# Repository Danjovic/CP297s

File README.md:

# CP297s
ZX97 lite board for CP200s case

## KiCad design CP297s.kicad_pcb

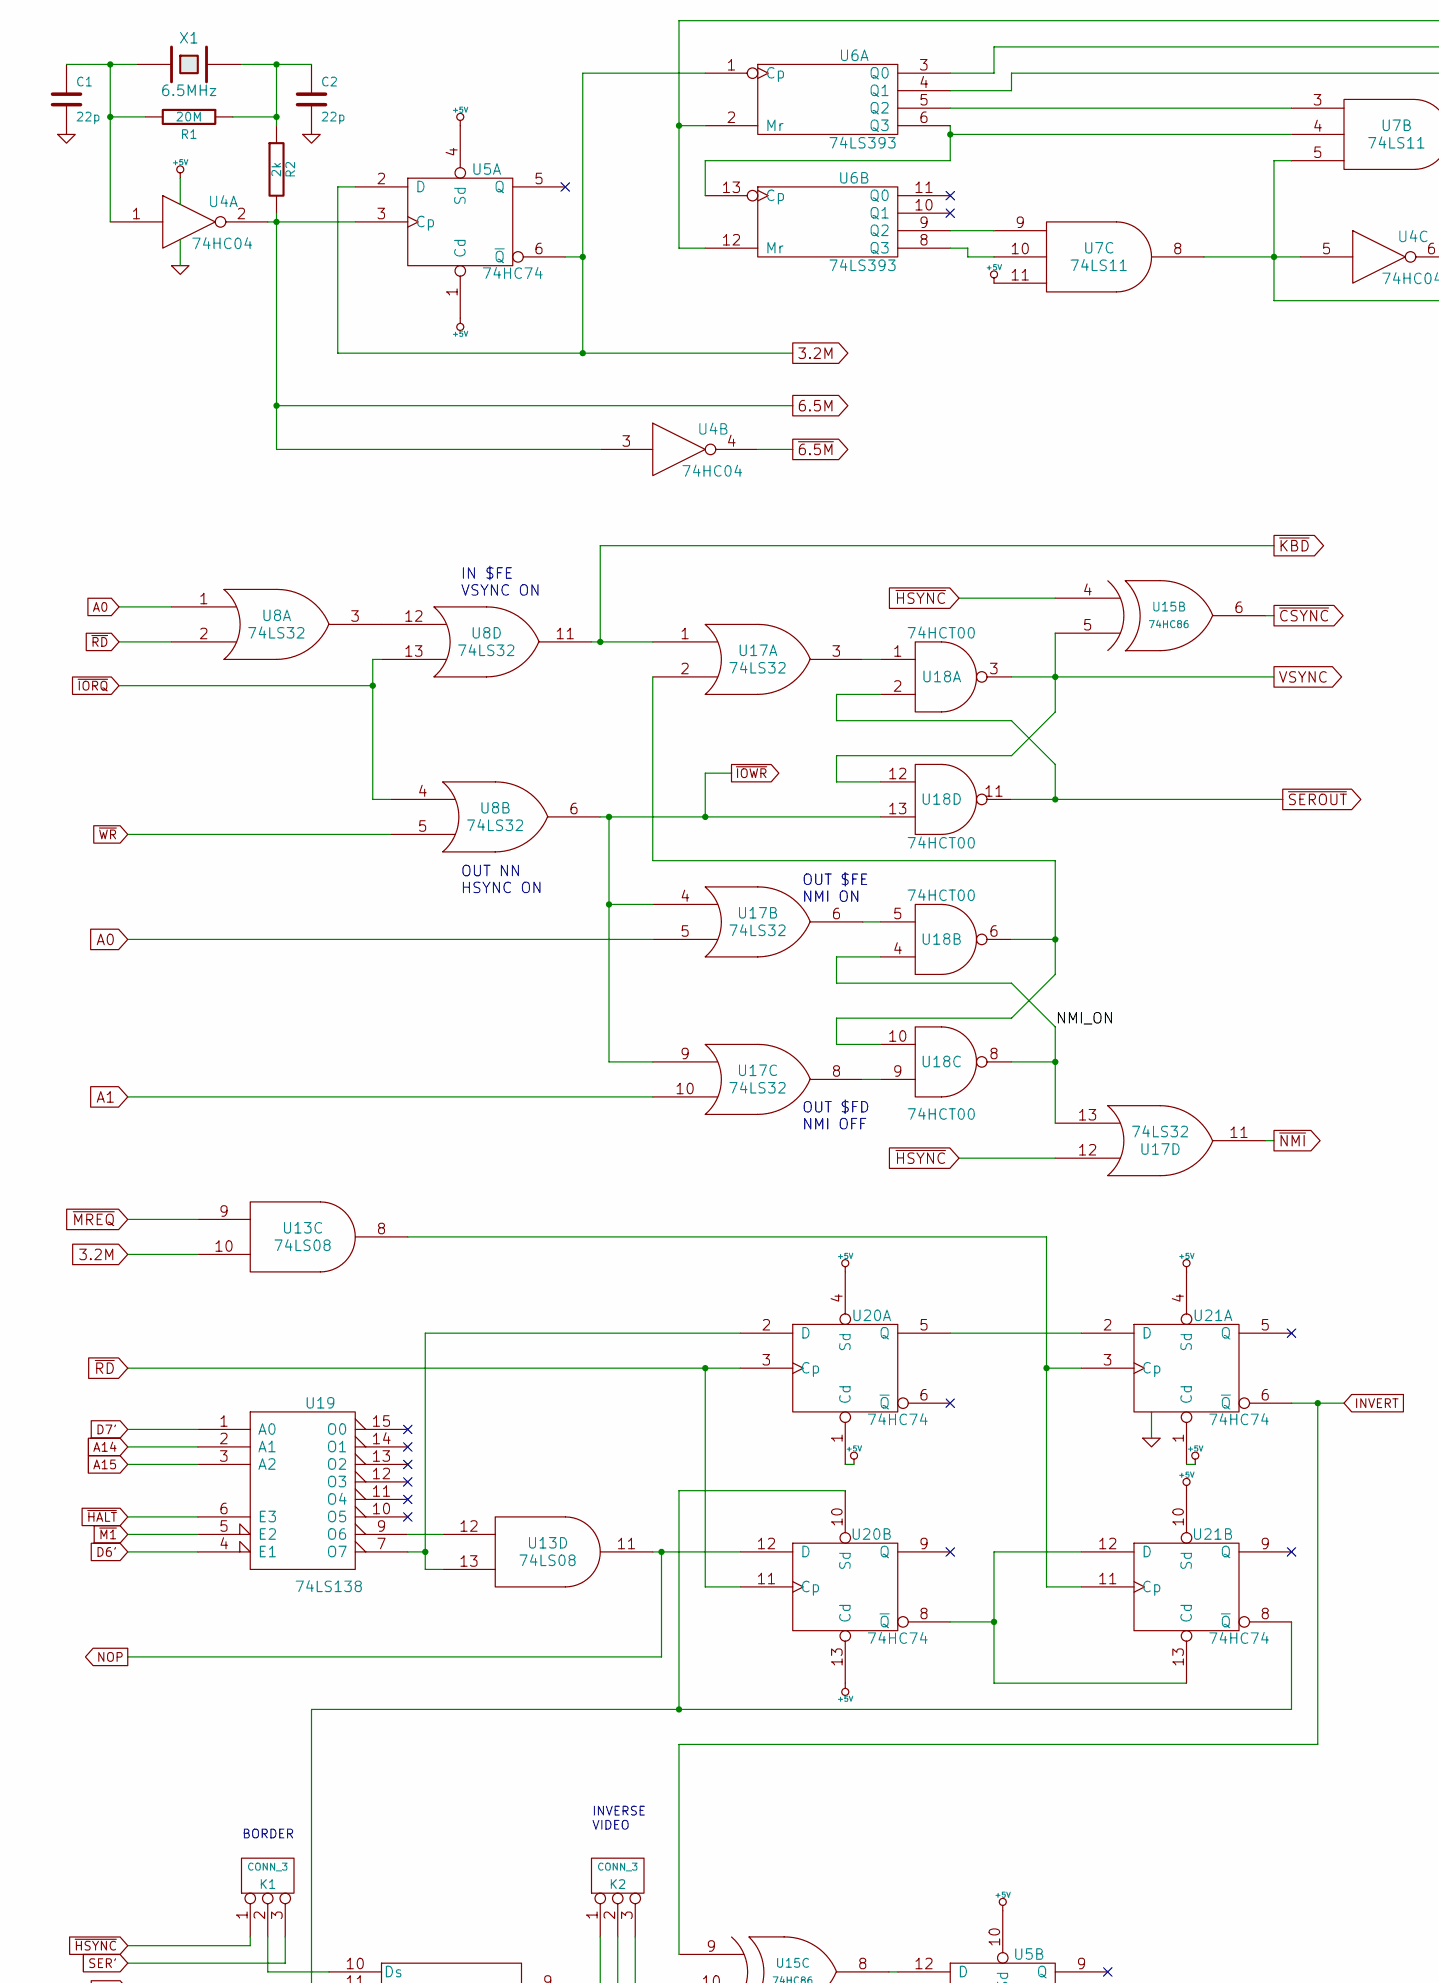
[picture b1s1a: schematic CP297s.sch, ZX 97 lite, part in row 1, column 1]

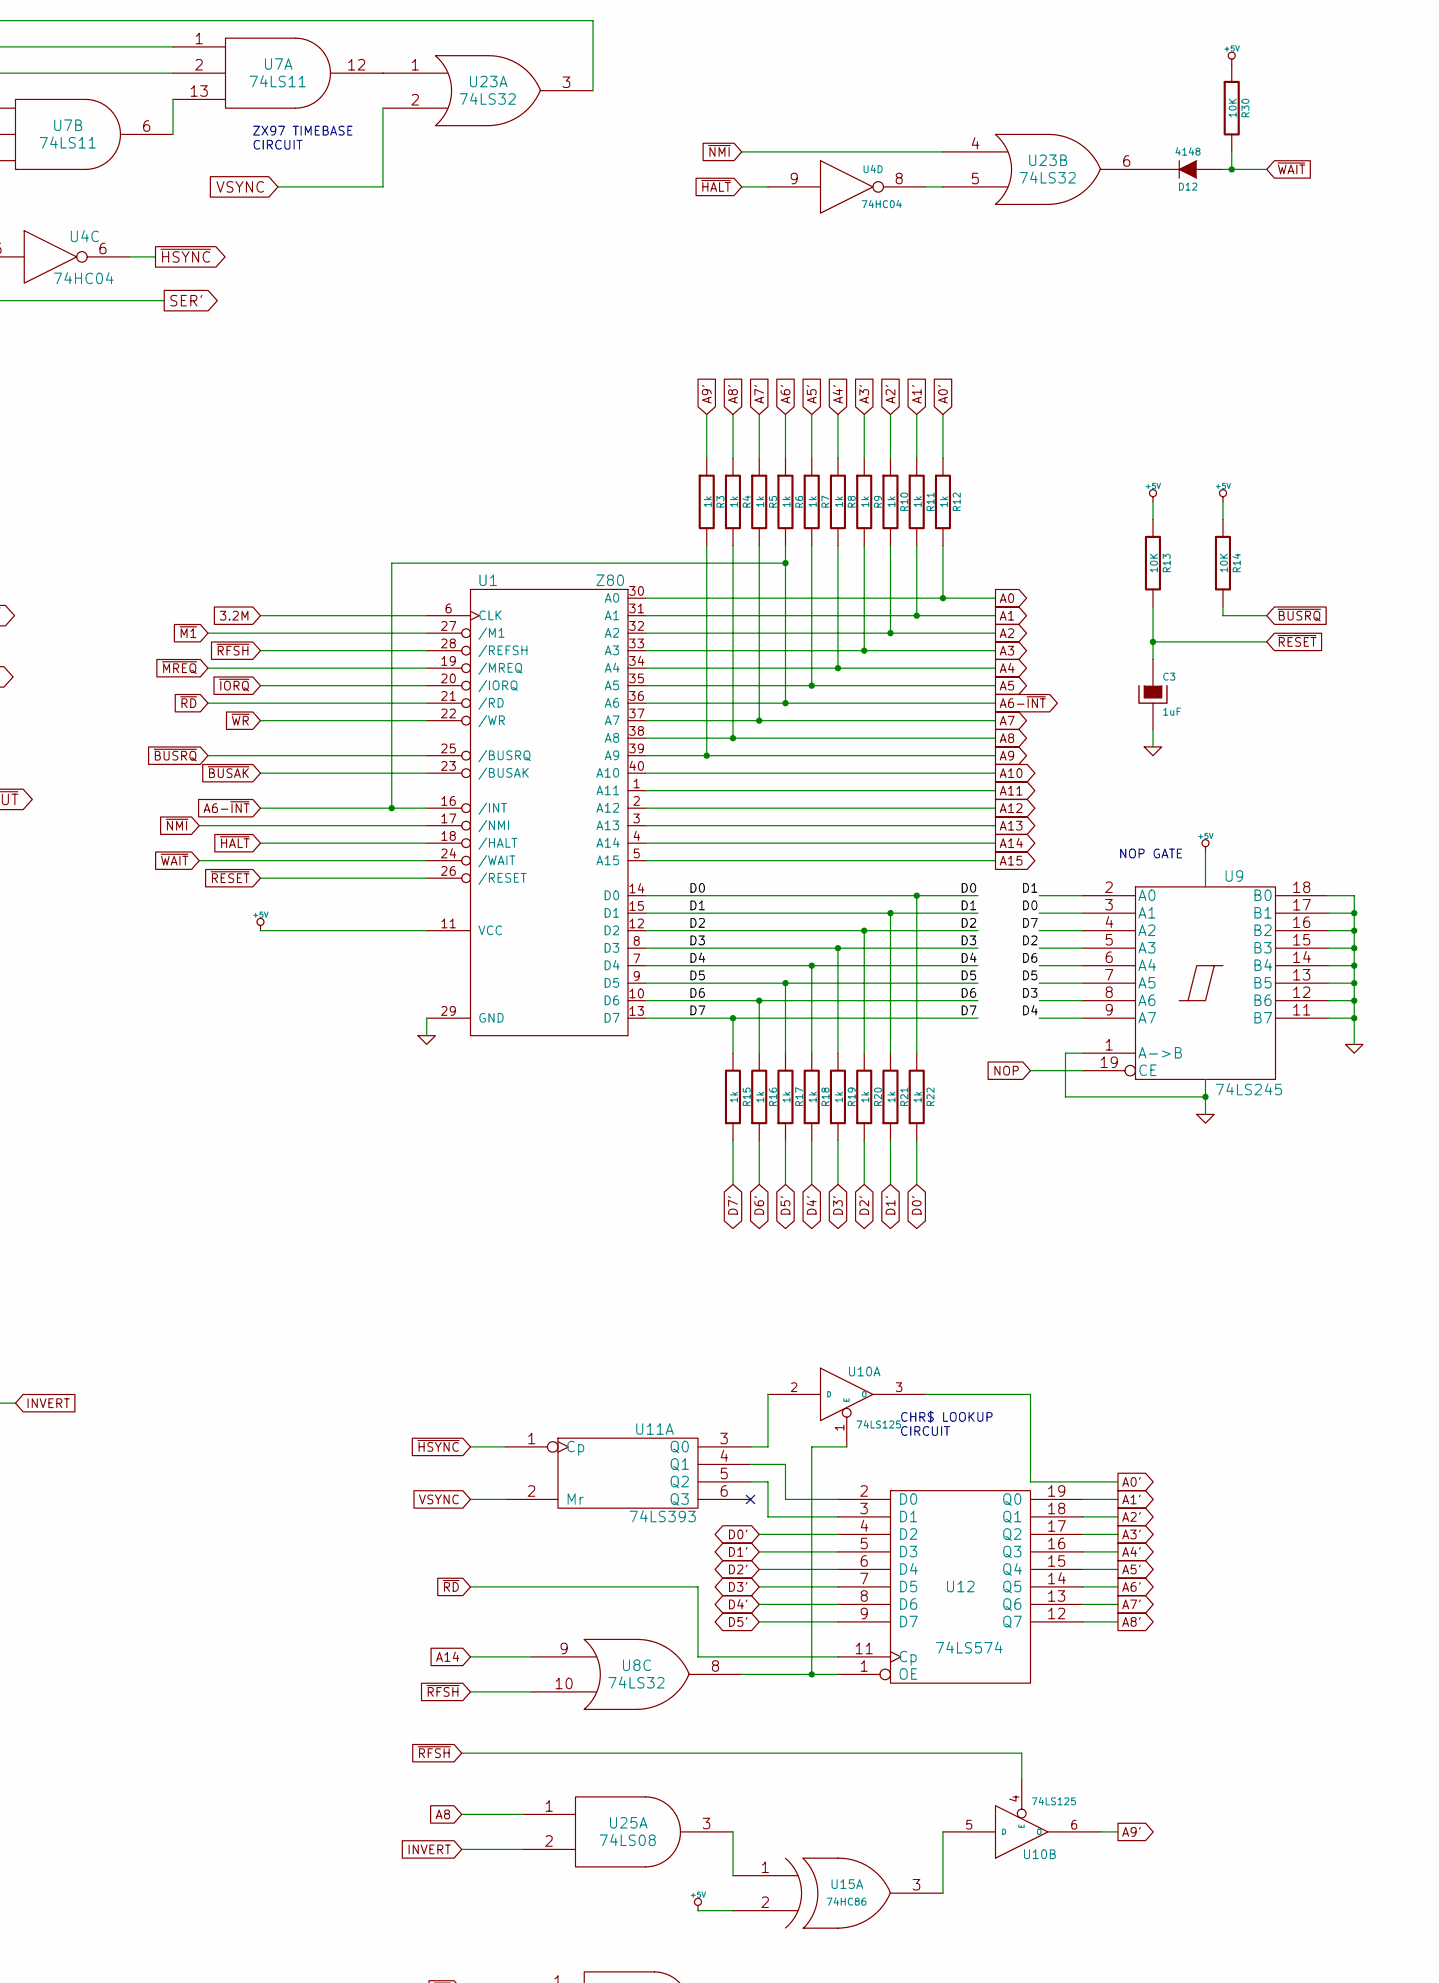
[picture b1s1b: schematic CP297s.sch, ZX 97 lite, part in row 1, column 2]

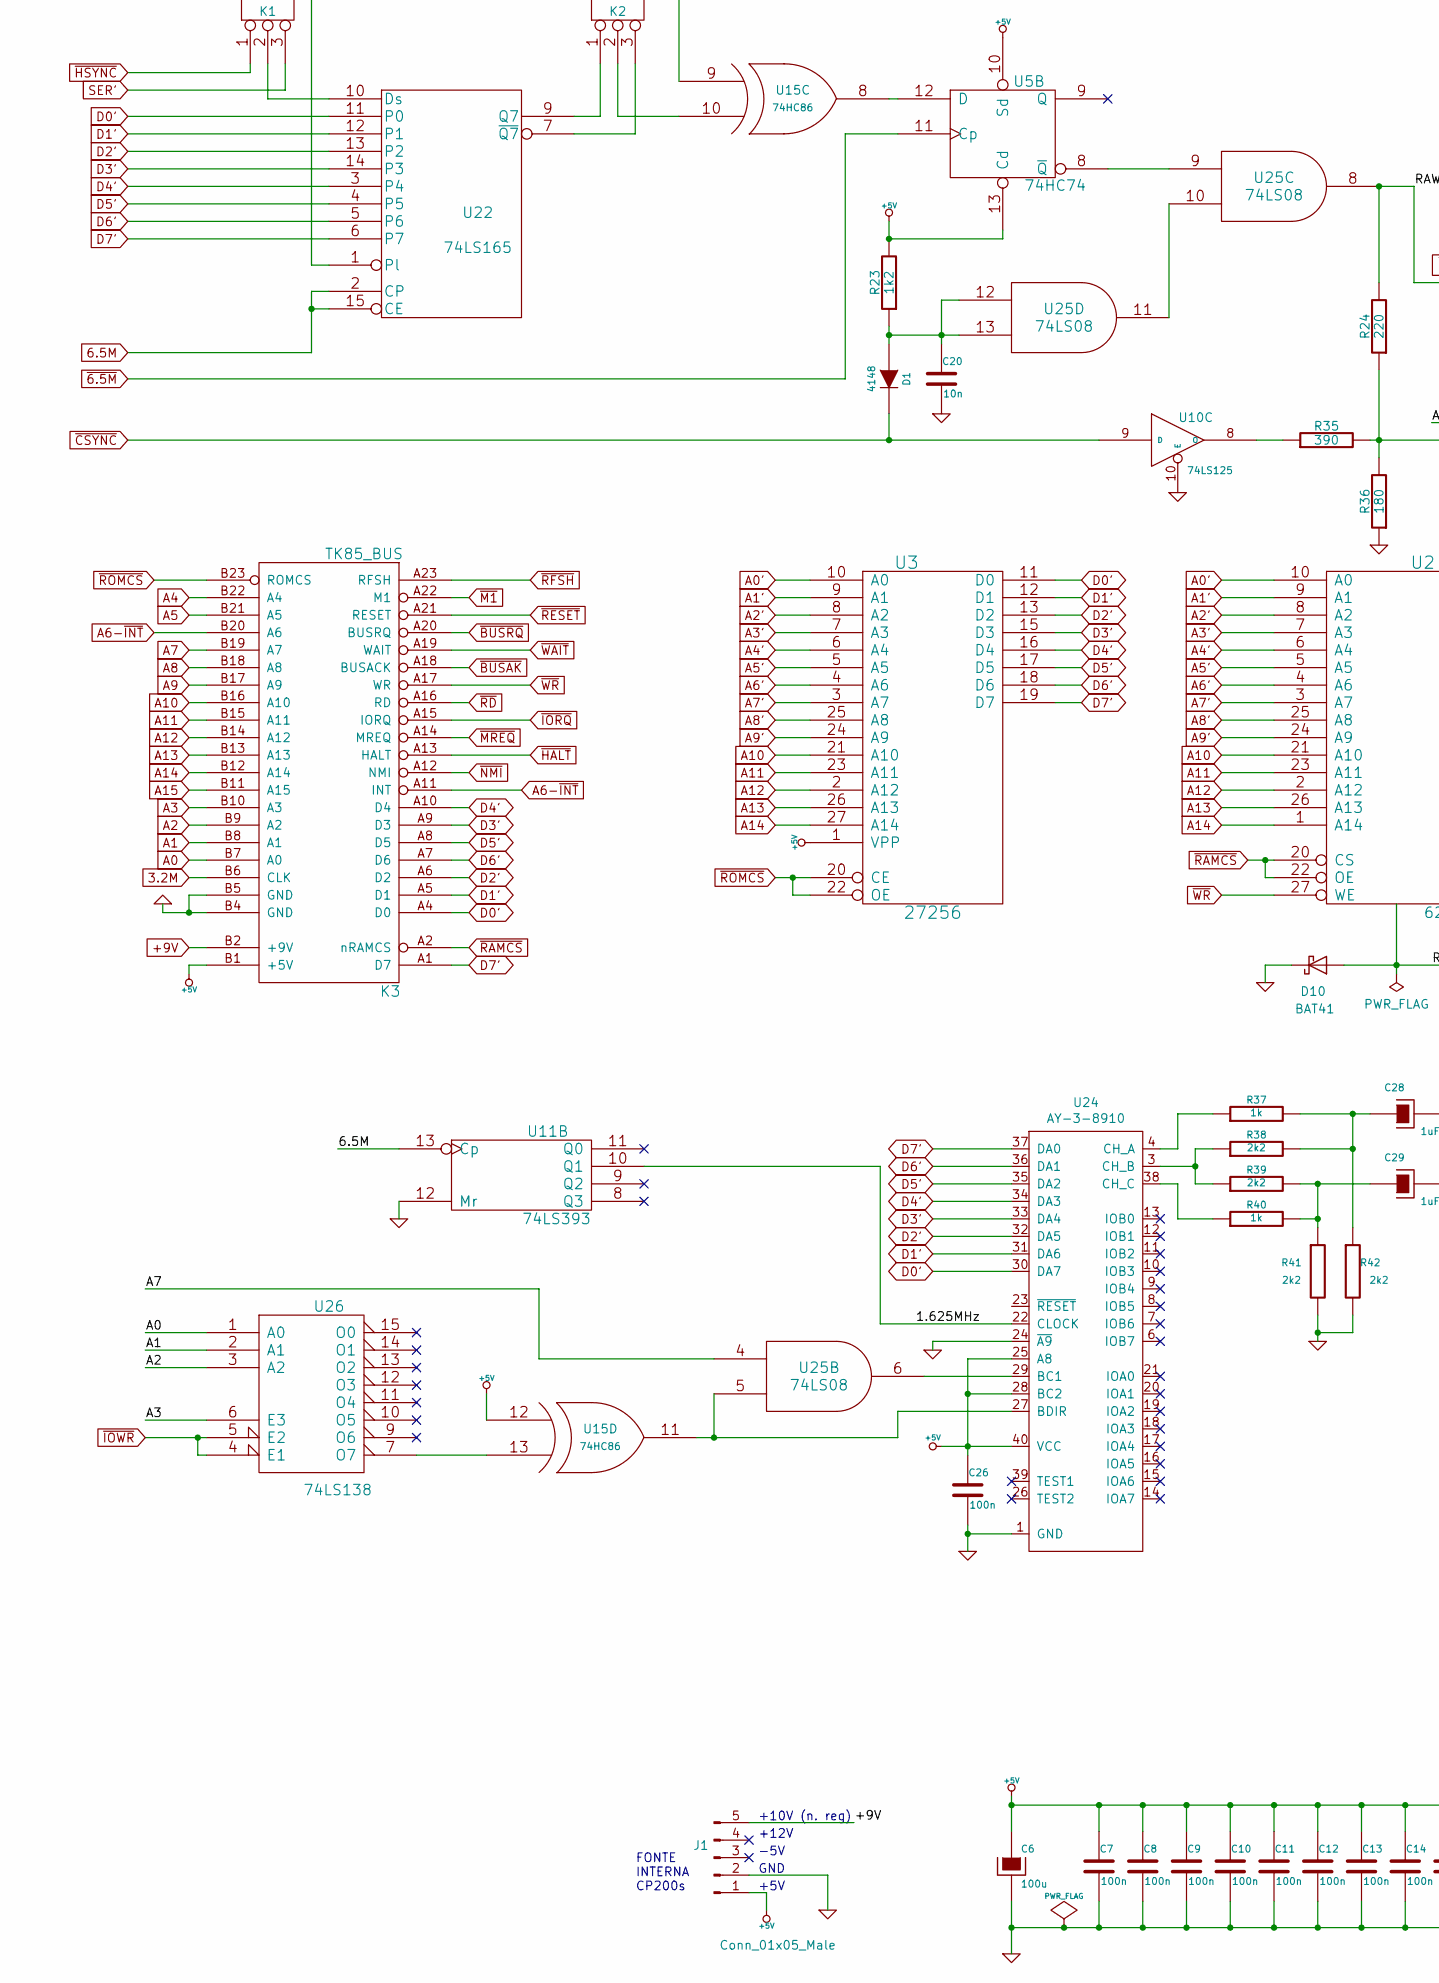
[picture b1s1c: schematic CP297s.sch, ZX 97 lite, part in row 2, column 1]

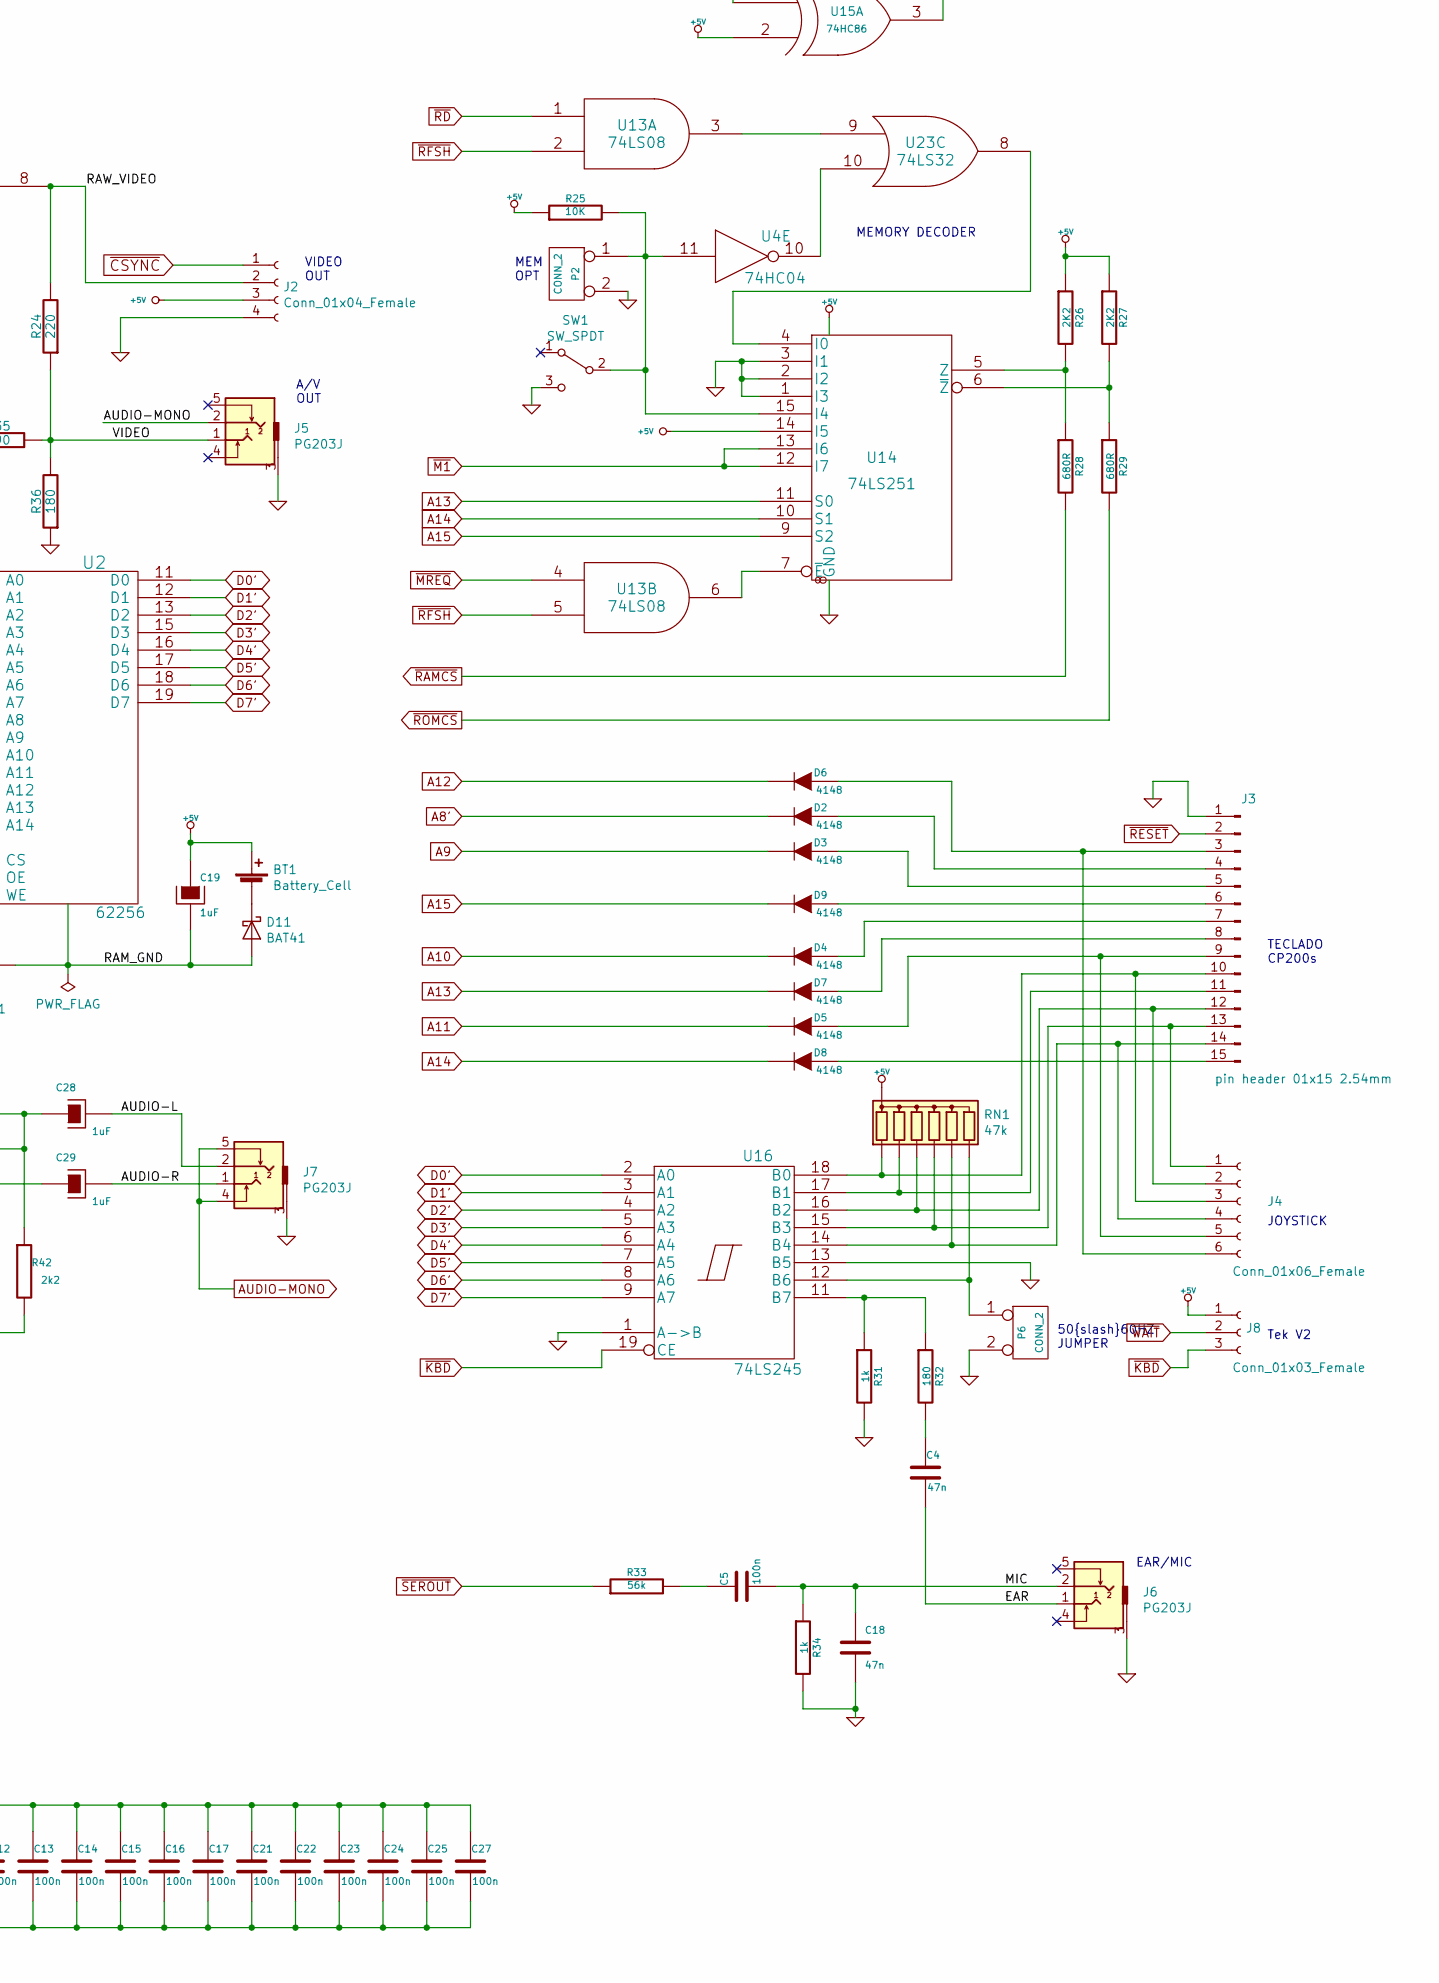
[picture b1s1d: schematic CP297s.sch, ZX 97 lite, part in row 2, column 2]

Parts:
BT1: Battery_Cell; BatteryHolder_CR2032H
C1, C2: 22p; C_Disc_D3.0mm_W1.6mm_P2.50mm
C3, C19, C28, C29: 1uF; CP_Radial_D5.0mm_P2.50mm
C4, C18: 47n; C_Disc_D7.0mm_W2.5mm_P5.00mm
C5, C7, C8, C9, C10, C11, C12, C13, C14, C15, C16, C17, C21, C22, C23, C24, C25, C26, C27: 100n; C_Disc_D7.0mm_W2.5mm_P5.00mm
C6: 100u; CP_Radial_D8.0mm_P3.50mm
C20: 10n; C_Disc_D7.0mm_W2.5mm_P5.00mm
D1, D2, D3, D4, D5, D6, D7, D8, D9, D12: 4148; D_A-405_P7.62mm_Horizontal
D10, D11: BAT41; D_A-405_P7.62mm_Horizontal
J1: Conn_01x05_Male; CP200S_FONTE
J2: Conn_01x04_Female; CP200S_VIDEO
J3: pin header 01x15 2.54mm; CP200s_Keyboard
J4: Conn_01x06_Female; CP200S_JOYSTICK
J5, J6, J7: PG203J
J8: Conn_01x03_Female; PinHeader_1x03_P2.54mm_Vertical
K1, K2: CONN_3; PinHeader_1x03_P2.54mm_Vertical
K3: TK85_BUS; ZX81_EDGE
P2, P6: CONN_2; PinHeader_1x02_P2.54mm_Vertical
R1: 20M; R_Axial_DIN0207_L6.3mm_D2.5mm_P7.62mm_Horizontal
R2: 2k; R_Axial_DIN0207_L6.3mm_D2.5mm_P7.62mm_Horizontal
R3, R4, R5, R6, R7, R8, R9, R10, R11, R12, R15, R16, R17, R18, R19, R20, R21, R22, R31, R34, R37, R40: 1k; R_Axial_DIN0207_L6.3mm_D2.5mm_P7.62mm_Horizontal
R13, R14, R25, R30: 10K; R_Axial_DIN0207_L6.3mm_D2.5mm_P7.62mm_Horizontal
R23: 1k2; R_Axial_DIN0207_L6.3mm_D2.5mm_P7.62mm_Horizontal
R24: 220; R_Axial_DIN0207_L6.3mm_D2.5mm_P7.62mm_Horizontal
R26, R27: 2K2; R_Axial_DIN0207_L6.3mm_D2.5mm_P7.62mm_Horizontal
R28, R29: 680R; R_Axial_DIN0207_L6.3mm_D2.5mm_P7.62mm_Horizontal
R32, R36: 180; R_Axial_DIN0207_L6.3mm_D2.5mm_P7.62mm_Horizontal
R33: 56k; R_Axial_DIN0207_L6.3mm_D2.5mm_P7.62mm_Horizontal
R35: 390; R_Axial_DIN0207_L6.3mm_D2.5mm_P7.62mm_Horizontal
R38, R39, R41, R42: 2k2; R_Axial_DIN0207_L6.3mm_D2.5mm_P7.62mm_Horizontal
RN1: 47k; R_Array_SIP7
SW1: SW_SPDT; SS-12F23_SPDT_Angled
U1: Z80; DIP-40_W15.24mm
U2: 62256; DIP-28_W15.24mm
U3: 27256; DIP-28_W15.24mm
U4: 74HC04; DIP-14_W7.62mm
U5, U20, U21: 74HC74; DIP-14_W7.62mm
U6, U11: 74LS393; DIP-14_W7.62mm
U7: 74LS11; DIP-14_W7.62mm
U8, U17, U23: 74LS32; DIP-14_W7.62mm
U9, U16: 74LS245; DIP-20_W7.62mm
U10: 74LS125; DIP-14_W7.62mm
U12: 74LS574; DIP-20_W7.62mm
U13, U25: 74LS08; DIP-14_W7.62mm
U14: 74LS251; DIP-16_W7.62mm
U15: 74HC86; DIP-14_W7.62mm
U18: 74HCT00; DIP-14_W7.62mm
U19, U26: 74LS138; DIP-16_W7.62mm
U22: 74LS165; DIP-16_W7.62mm
U24: AY-3-8910; DIP-40_W15.24mm
X1: 6.5MHz; Crystal_HC49-U_Vertical

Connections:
3.2M: K3.B6 (CLK), U1.6 (CLK), U5.2 (D), U5.6 (~Q), U6.1 (Cp), U13.10
6.5M: R2.2, U4.2, U4.3, U5.3 (Cp), U22.2 (CP), U22.15 (CE)
+5V: BT1.1 (+), C6.1, C7.1, C8.1, C9.1, C10.1, C11.1, C12.1, C13.1, C14.1, C15.1, C16.1, C17.1, C19.1, C21.1, C22.1, C23.1, C24.1, C25.1, C26.1, C27.1, J1.1, J2.3, J8.1, K3.B1 (+5V), R13.1, R14.1, R23.2, R25.1, R26.1, R27.1, R30.1, RN1.1 (common), U1.11 (VCC), U2.28 (VCC), U3.1 (VPP), U3.28 (VCC), U4.14 (VCC), U5.1 (Cd), U5.4 (Sd), U5.10 (Sd), U5.13 (Cd), U5.14 (VCC), U6.14 (VCC), U7.11, U7.14 (VCC), U8.14 (VCC), U9.20 (VCC), U10.14 (VCC), U11.14 (VCC), U12.20 (VCC), U13.14 (VCC), U14.14 (I5), U14.16 (VCC), U15.2 (IN2), U15.12 (IN1), U15.14 (VCC), U16.20 (VCC), U17.14 (VCC), U18.14 (VCC), U19.16 (VCC), U20.1 (Cd), U20.4 (Sd), U20.13 (Cd), U20.14 (VCC), U21.1 (Cd), U21.4 (Sd), U21.10 (Sd), U21.14 (VCC), U22.16 (VCC), U23.14 (VCC), U24.25 (A8), U24.28 (BC2), U24.40 (VCC), U25.14 (VCC), U26.16 (VCC)
+9V: K3.B2 (+9V)
/1.625MHz: U11.10 (Q1), U24.22 (CLOCK)
/6.5M: U11.13 (Cp)
/+9V: J1.5
/A0: U26.1 (A0)
/A1: U26.2 (A1)
/A2: U26.3 (A2)
/A3: U26.6 (E3)
/A7: U25.4
/AUDIO-L: C28.2, J7.2
/AUDIO-MONO: J5.2
/AUDIO-R: C29.2, J7.1
/D0: R22.2, U1.14 (D0), U9.3 (A1)
/D1: R21.2, U1.15 (D1), U9.2 (A0)
/D2: R20.2, U1.12 (D2), U9.5 (A3)
/D3: R19.2, U1.8 (D3), U9.8 (A6)
/D4: R18.2, U1.7 (D4), U9.9 (A7)
/D5: R17.2, U1.9 (D5), U9.7 (A5)
/D6: R16.2, U1.10 (D6), U1.~ (D6), U9.6 (A4)
/D7: R15.2, U1.13 (D7), U9.4 (A2)
/EAR: C4.2, J6.1
/MIC: C5.2, C18.2, J6.2, R34.1
/NMI_ON: U17.13, U18.4, U18.8
/RAW_VIDEO: J2.2, R24.2, U25.8
/VIDEO: J5.1, R24.1, R35.2, R36.2
A0: K3.B7 (A0), R12.2, U1.30 (A0), U8.1, U17.5
A0': R12.1, U2.10 (A0), U3.10 (A0), U10.3 (O)
A1: K3.B8 (A1), R11.2, U1.31 (A1), U17.10
A1': R11.1, U2.9 (A1), U3.9 (A1), U12.19 (Q0)
A2: K3.B9 (A2), R10.2, U1.32 (A2)
A2': R10.1, U2.8 (A2), U3.8 (A2), U12.18 (Q1)
A3: K3.B10 (A3), R9.2, U1.33 (A3)
A3': R9.1, U2.7 (A3), U3.7 (A3), U12.17 (Q2)
A4: K3.B22 (A4), R8.2, U1.34 (A4)
A4': R8.1, U2.6 (A4), U3.6 (A4), U12.16 (Q3)
A5: K3.B21 (A5), R7.2, U1.35 (A5)
A5': R7.1, U2.5 (A5), U3.5 (A5), U12.15 (Q4)
A6': R6.1, U2.4 (A6), U3.4 (A6), U12.14 (Q5)
A6-~INT: K3.A11 (INT), K3.B20 (A6), R6.2, U1.16 (/INT), U1.36 (A6)
A7: K3.B19 (A7), R5.2, U1.37 (A7)
A7': R5.1, U2.3 (A7), U3.3 (A7), U12.13 (Q6)
A8: K3.B18 (A8), R4.2, U1.38 (A8), U25.1
A8': D2.2 (K), R4.1, U2.25 (A8), U3.25 (A8), U12.12 (Q7)
A9: D3.2 (K), K3.B17 (A9), R3.2, U1.39 (A9)
A9': R3.1, U2.24 (A9), U3.24 (A9), U10.6 (O)
A10: D4.2 (K), K3.B16 (A10), U1.40 (A10), U2.21 (A10), U3.21 (A10)
A11: D5.2 (K), K3.B15 (A11), U1.1 (A11), U2.23 (A11), U3.23 (A11)
A12: D6.2 (K), K3.B14 (A12), U1.2 (A12), U2.2 (A12), U3.2 (A12)
A13: D7.2 (K), K3.B13 (A13), U1.3 (A13), U2.26 (A13), U3.26 (A13), U14.11 (S0)
A14: D8.2 (K), K3.B12 (A14), U1.4 (A14), U2.1 (A14), U3.27 (A14), U8.9, U14.10 (S1), U19.2 (A1)
A15: D9.2 (K), K3.B11 (A15), U1.5 (A15), U14.9 (S2), U19.3 (A2)
AUDIO-MONO: J7.4, J7.5
D0': K3.A4 (D0), R22.1, U2.11 (D0), U3.11 (D0), U12.4 (D2), U16.2 (A0), U22.11 (P0), U24.30 (DA7)
D1': K3.A5 (D1), R21.1, U2.12 (D1), U3.12 (D1), U12.5 (D3), U16.3 (A1), U22.12 (P1), U24.31 (DA6)
D2': K3.A6 (D2), R20.1, U2.13 (D2), U3.13 (D2), U12.6 (D4), U16.4 (A2), U22.13 (P2), U24.32 (DA5)
D3': K3.A9 (D3), R19.1, U2.15 (D3), U3.15 (D3), U12.7 (D5), U16.5 (A3), U22.14 (P3), U24.33 (DA4)
D4': K3.A10 (D4), R18.1, U2.16 (D4), U3.16 (D4), U12.8 (D6), U16.6 (A4), U22.3 (P4), U24.34 (DA3)
D5': K3.A8 (D5), R17.1, U2.17 (D5), U3.17 (D5), U12.9 (D7), U16.7 (A5), U22.4 (P5), U24.35 (DA2)
D6': K3.A7 (D6), R16.1, U2.18 (D6), U3.18 (D6), U16.8 (A6), U19.4 (E1), U22.5 (P6), U24.36 (DA1)
D7': K3.A1 (D7), R15.1, U2.19 (D7), U3.19 (D7), U16.9 (A7), U19.1 (A0), U22.6 (P7), U24.37 (DA0)
GND: C1.2, C2.2, C3.2, C6.2, C7.2, C8.2, C9.2, C10.2, C11.2, C12.2, C13.2, C14.2, C15.2, C16.2, C17.2, C18.1, C20.2, C21.2, C22.2, C23.2, C24.2, C25.2, C26.2, C27.2, D10.1 (K), J1.2, J2.4, J3.1, J5.3, J6.3, J7.3, K3.B4 (GND), K3.B5 (GND), P2.2 (PM), P6.2 (PM), R31.2, R34.2, R36.1, R41.2, R42.2, SW1.3 (C), U1.29 (GND), U3.14 (GND), U4.7 (GND), U5.7 (GND), U6.7 (GND), U7.7 (GND), U8.7 (GND), U9.1 (A->B), U9.10 (GND), U9.11 (B7), U9.12 (B6), U9.13 (B5), U9.14 (B4), U9.15 (B3), U9.16 (B2), U9.17 (B1), U9.18 (B0), U10.7 (GND), U10.10 (E), U11.7 (GND), U11.12 (Mr), U12.10 (GND), U13.7 (GND), U14.1 (I3), U14.2 (I2), U14.3 (I1), U14.8 (GND), U15.7 (GND), U16.1 (A->B), U16.10 (GND), U16.13 (B5), U17.7 (GND), U18.7 (GND), U19.8 (GND), U20.7 (GND), U21.7 (GND), U22.8 (GND), U23.7 (GND), U24.1 (GND), U24.24 (~A9), U25.7 (GND), U26.8 (GND)
INVERT: U15.9 (IN1), U21.6 (~Q), U25.2
NOP: U9.19 (CE), U13.11, U20.12 (D)
unnamed: BT1.2 (-), D11.1 (K)
unnamed: C1.1, R1.2, U4.1, X1.1
unnamed: C2.1, R1.1, R2.1, X1.2
unnamed: C4.1, R32.2
unnamed: C5.1, R33.2
unnamed: C20.1, D1.1 (A), R23.1, U25.12, U25.13
unnamed: C28.1, R37.2, R38.2, R42.1
unnamed: C29.1, R39.2, R40.2, R41.1
unnamed: D2.1 (A), J3.4
unnamed: D3.1 (A), J3.5
unnamed: D4.1 (A), J3.7
unnamed: D5.1 (A), J3.9, J4.5
unnamed: D6.1 (A), J3.3, J4.6
unnamed: D7.1 (A), J3.8
unnamed: D8.1 (A), J3.15
unnamed: D9.1 (A), J3.6
unnamed: D12.2 (K), U23.6
unnamed: J3.10, J4.3, RN1.2 (R1), U16.18 (B0)
unnamed: J3.11, RN1.3 (R2), U16.17 (B1)
unnamed: J3.12, J4.2, RN1.4 (R3), U16.16 (B2)
unnamed: J3.13, J4.1, RN1.5 (R4), U16.15 (B3)
unnamed: J3.14, J4.4, RN1.6 (R5), U16.14 (B4)
unnamed: K1.2 (PM), U22.10 (Ds)
unnamed: K2.1, U22.9 (Q7)
unnamed: K2.2 (PM), U15.10 (IN2)
unnamed: K2.3, U22.7 (~Q7)
unnamed: P2.1, R25.2, SW1.2 (B), U4.11, U14.15 (I4)
unnamed: P6.1, RN1.7 (R6), U16.12 (B6)
unnamed: R26.2, R28.1, U14.5 (Z)
unnamed: R27.2, R29.1, U14.6 (~Z)
unnamed: R31.1, R32.1, U16.11 (B7)
unnamed: R35.1, U10.8 (O)
unnamed: R37.1, U24.4 (CH_A)
unnamed: R38.1, R39.1, U24.3 (CH_B)
unnamed: R40.1, U24.38 (CH_C)
unnamed: U6.3 (Q0), U7.1
unnamed: U6.4 (Q1), U7.2
unnamed: U6.5 (Q2), U7.3
unnamed: U6.8 (Q3), U7.10
unnamed: U6.9 (Q2), U7.9
unnamed: U6.6 (Q3), U6.13 (Cp), U7.4
unnamed: U7.6, U7.13
unnamed: U8.3, U8.12
unnamed: U8.8, U10.1 (E), U12.1 (OE)
unnamed: U10.2 (D), U11.3 (Q0)
unnamed: U10.5 (D), U15.3 (OUT)
unnamed: U11.4 (Q1), U12.2 (D0)
unnamed: U11.5 (Q2), U12.3 (D1)
unnamed: U13.3, U23.9
unnamed: U13.6, U14.7 (~E)
unnamed: U13.8, U21.3 (Cp), U21.11 (Cp)
unnamed: U13.12, U19.9 (O6)
unnamed: U13.13, U19.7 (O7), U20.2 (D)
unnamed: U14.4 (I0), U23.8
unnamed: U15.1 (IN1), U25.3
unnamed: U5.12 (D), U15.8 (OUT)
unnamed: U15.11 (OUT), U24.27 (BDIR), U25.5
unnamed: U15.13 (IN2), U26.7 (O7)
unnamed: U17.2, U18.6, U18.10
unnamed: U17.3, U18.1
unnamed: U17.6, U18.5
unnamed: U17.8, U18.9
unnamed: U20.5 (Q), U21.2 (D)
unnamed: U20.8 (~Q), U21.12 (D), U21.13 (Cd)
unnamed: U20.10 (Sd), U21.8 (~Q), U22.1 (Pl)
unnamed: U7.12, U23.1
unnamed: U6.2 (Mr), U6.12 (Mr), U23.3
unnamed: U4.8, U23.5
unnamed: U4.10, U23.10
unnamed: U24.29 (BC1), U25.6
unnamed: U5.8 (~Q), U25.9
unnamed: U25.10, U25.11
SER': K1.3, U4.5, U7.5, U7.8
VSYNC: U11.2 (Mr), U15.5 (IN2), U18.3, U18.12, U23.2
~: C19.2, D10.2 (A), D11.2 (A), U2.14
~6.5M: U4.4, U5.11 (Cp)
~BUSAK: K3.A18 (BUSACK), U1.23 (/BUSAK)
~BUSRQ: K3.A20 (BUSRQ), R14.2, U1.25 (/BUSRQ)
~CSYNC: D1.2 (K), J2.1, U10.9 (D), U15.6 (OUT)
~HALT: K3.A13 (HALT), U1.18 (/HALT), U4.9, U19.6 (E3)
~HSYNC: K1.1, U4.6, U11.1 (Cp), U15.4 (IN1), U17.12
~IORQ: K3.A15 (IORQ), U1.20 (/IORQ), U8.4, U8.13
~IOWR: U8.6, U17.4, U17.9, U18.13, U26.4 (E1), U26.5 (E2)
~KBD: J8.3, U8.11, U16.19 (CE), U17.1
~M1: K3.A22 (M1), U1.27 (/M1), U14.12 (I7), U14.13 (I6), U19.5 (E2)
~MREQ: K3.A14 (MREQ), U1.19 (/MREQ), U13.4, U13.9
~NMI: K3.A12 (NMI), U1.17 (/NMI), U17.11, U23.4
~RAMCS: K3.A2 (nRAMCS), R28.2, U2.20 (CS), U2.22 (OE)
~RD: K3.A16 (RD), U1.21 (/RD), U8.2, U12.11 (Cp), U13.1, U20.3 (Cp), U20.11 (Cp)
~RESET: C3.1, J3.2, K3.A21 (RESET), R13.2, U1.26 (/RESET)
~RFSH: K3.A23 (RFSH), U1.28 (/REFSH), U8.10, U10.4 (E), U13.2, U13.5
~ROMCS: K3.B23 (ROMCS), R29.2, U3.20 (CE), U3.22 (OE)
~SEROUT: R33.1, U18.2, U18.11
~WAIT: D12.1 (A), J8.2, K3.A19 (WAIT), R30.2, U1.24 (/WAIT)
~WR: K3.A17 (WR), U1.22 (/WR), U2.27 (WE), U8.5

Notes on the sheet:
IN $FE VSYNC ON
OUT NN HSYNC ON
OUT $FE NMI ON
OUT $FD NMI OFF
CHR$ LOOKUP CIRCUIT
NOP GATE
ZX97 TIMEBASE CIRCUIT
MEMORY DECODER
MEM OPT
INVERSE VIDEO
50{slash}60HZ JUMPER
EAR/MIC
VIDEO OUT
JOYSTICK
TECLADO CP200s
FONTE INTERNA CP200s
+10V (n. reg)
+12V
-5V
GND
+5V
A/V OUT
BORDER
Tek V2
